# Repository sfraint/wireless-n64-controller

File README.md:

# wireless-n64-controller

## SMD Version

**This branch is for the SMD version of the controller. This is even more experimental than the original.**

**Much of the documentation is out-dated for this version, but publishing this branch for others to look at until I can polish it a bit.**

## Overview

This project and its documentation is a Work-In-Progress. I'm still working on writing everything down and working out kinks in the design files and prototypes.

**The idea is to publish the design files and software used to upgrade an OEM or cheap, wired N64 controller to a wireless, Bluetooth controller**. Hopefully these published files can assist others in completing similar projects.

## Motivation
When this project was started, no original-form-factor bluetooth N64 wireless controllers were available for purchase. There were some two-handle controllers, inspired by N64 original controllers, but none with the original three-handle setup.

The main goal of this project was to upgrade an existing OEM or cheap three-handle N64 wired controller to use bluetooth, so it could be used with a PC and/or Raspberry Pi.

## Operation

Using the controller is pretty straightforward:

1. Insert a charged battery pak into the controller to turn it on. Note: if the LED is installed, it should light up once the controller is powered on.

2. After a few seconds, pair the controller to a client machine (e.g. phone or PC). The controller should show up as `ESP32 BLE Gamepad` in bluetooth device managers. Note: if the LED is installed, it will start blinking when the controller automatically enters pairing mode after power-up.

3. If the LED is installed, it will blink slowly when the controller is paired with a client machine.

### Analog Calibration

If you press and hold the `Start` button before the controller enters pairing mode, it will enter analog calibration mode, indicated by a rapidly blinking LED.

Upon entering calibration mode, the initial position of the joystick is recorded as the new `center` position. During calibration mode, you should rotate the joystick around in circles, reaching the all the extremes (far up, right, down, left) to reset `min` and `max` values for both the X and Y axes.

Calibration mode lasts for a few seconds (~5 sec). Upon completion, it writes results to non-volatile storage if possible, then resumes normal startup routing - entering pairing mode.

### "Soft" Buttons

This wireless N64 controller has all the normal N64 buttons plus a few extra software buttons, triggered by special button combinations. These software buttons can be associated with special functions in some emulators, like triggering the menu function, save/load state, etc.

There are currently three "soft" buttons, all triggered by pressing the center of the d-pad (i.e. pressing all 4 directions at the same time) plus either `Start`, `A`, or `B`.

## Building your own
More detailed building instructions can be found [here](building.md).

*Note: this project requires soldering and some basic understanding of electriconics and circuits. I also assume you already have soldering equipment and some ~30 gauge wire to wire up components.*

### Steps

1. Purchase the base parts. See the [BOM for more details and links](BOM.md).
   * Base N64 controller you plan to modify. I'm not sure how standardized N64 controller internals are, so it is probably a good idea to confirm the measurements of your controller match up with the spacing of the PCB mounting/securing holes.
   * ESP32 microcontroller
   * AAA terminals
   * LiPo battery
   * LiPo battery charging board

2. Print the PCB.

3. Print the battery pak pieces. Alternatively, you could skip using a battery pak and directly wire a battery to the power-in on the microcontroller.

4. Program the microcontroller.

5. Solder the microcontroller and aux boards/wires to the PCB.

6. Assemble the N64 controller.

7. Have fun! (optional)

## Debugging
**Note: make sure you disconnect the battery before plugging a USB cable into the microcontroller. If you do not do this, you could permanently damage the controller or worse, whatever is on the other end of the USB cable, e.g. your PC.**

At any point, you can remove the PCB + microcontroller from the N64 controller and monitor or reprogram the microcontroller. **TODO** add debugging details.

## Components

### Microcontroller
An [ESP32](https://en.wikipedia.org/wiki/ESP32) microcontroller is used to:

1. read the raw button presses from the button hardware in the controller

2. convert that into a USB HID report

3. send the report via Bluetooth LE to a connected client, e.g. PC

It is also capable of a few other things like: tracking battery level, resetting Bluetooth connections, etc.

### PCB
A custom PCB was built to replace the existing controller PCB, mainly to a) make space for the ESP32 dev board I used and b) reduce the amount of soldering required.

### Battery Pak
A 3d-printed battery pack that fits into the controller "pak" port was used to supply power to the controller, since it can no longer pull power from the controller cable.

This "pak" fits a small lithium polymer battery as well as charging circuitry, and connects to the controller via typical AAA spring-terminals. The "pak" was designed to fit a 6mm x 40mm x 50mm battery, but could of course fit smaller batteries with adequate padding or adhesives.

## Performance

Rough performance numbers for the initial prototype controller are:

1. battery lifetime - using a ~1500 mAh lithium polymer battery, I expect the controller to last about ~15 hours of continuous use; I'm less sure about low-power mode lifetime, but probably a few weeks (longer if you just detach the battery).

2. controller latency - over 100 sequential button presses had a latency of between 2 and 13 ms (plus an additional ~2 ms for current software's polling interval - can reduce this using interrupts instead of polling, though chances are analog/jostick inputs will always suffer this extra latency)

   To measure approximate latency, I setup a second ESP32 which was:
   
   * a BLE client subscribed to the gamepad reports

   * running a GPIO interrupt to detect the button press

   Then, the second ESP32 recorded the time the button-interrupt was received as well as the time the BLE button-press-report was received. Got the approximate latency by subtracting the interrupt time from the BLE report time.

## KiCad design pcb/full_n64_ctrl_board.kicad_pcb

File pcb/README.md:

### PCB

This was designed with KiCad version 5.1.10

See [ordering](ordering.md) for details on ordering a PCB.

#### Front

#### Back

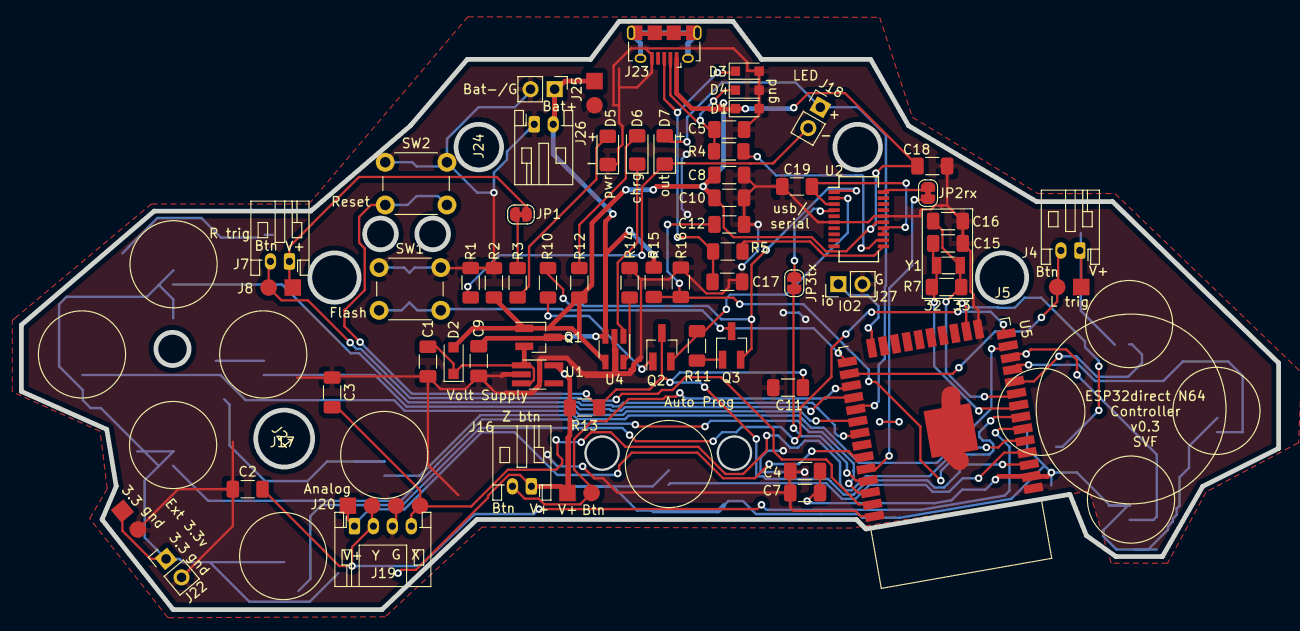
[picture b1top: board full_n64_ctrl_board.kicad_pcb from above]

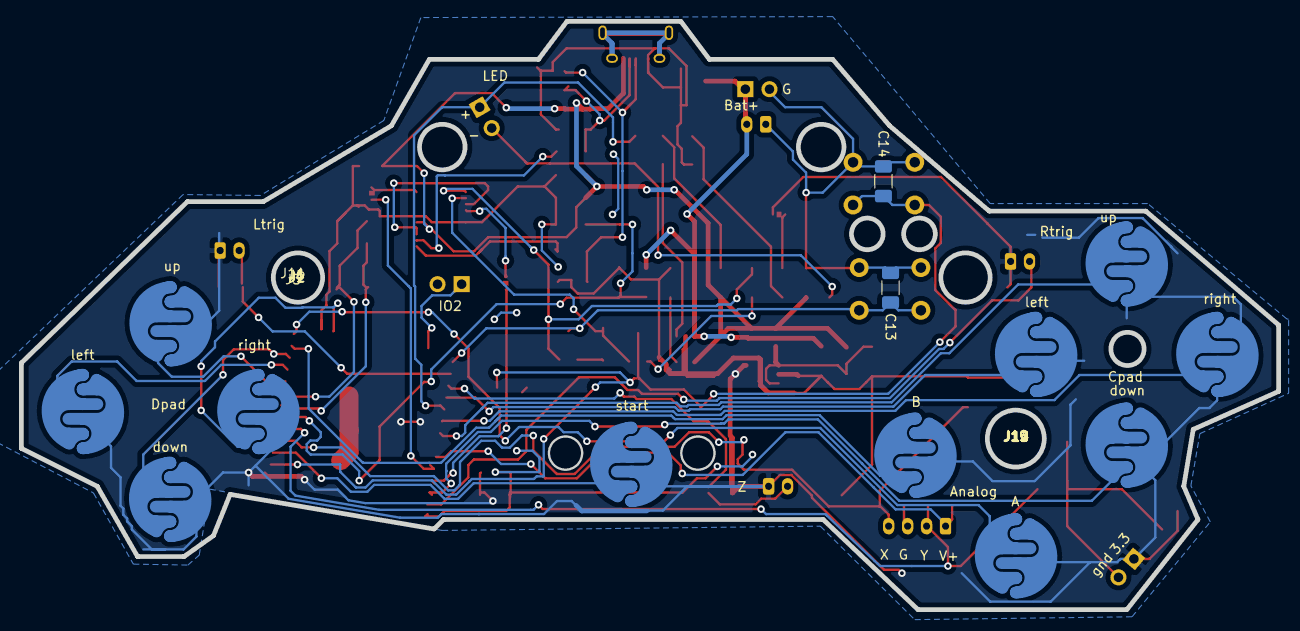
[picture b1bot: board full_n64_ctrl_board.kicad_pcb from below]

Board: 2 copper layers, 132.5 x 62.0 mm, 78 parts (13 on the bottom side), 48 nets.

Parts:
C1, C9, C10, C11, C18: 4.7uF; C_1206_3216Metric_Pad1.33x1.80mm_HandSolder
C2, C3: 0.1uF/50V; C_1206_3216Metric_Pad1.33x1.80mm_HandSolder
C4: 22uF; C_1206_3216Metric_Pad1.33x1.80mm_HandSolder
C5, C17: 47pF; C_1206_3216Metric_Pad1.33x1.80mm_HandSolder
C7, C8, C12, C13, C14, C19: 0.1uF; C_1206_3216Metric_Pad1.33x1.80mm_HandSolder
C15, C16: 7pF; C_1206_3216Metric_Pad1.33x1.80mm_HandSolder
D1, D3, D4: D_TVS; D_SOD-323_HandSoldering
D2: D_Schottky; D_SOD-123F
D5: PowerLED; LED_1206_3216Metric_Pad1.42x1.75mm_HandSolder
D6: ChargeLED; LED_1206_3216Metric_Pad1.42x1.75mm_HandSolder
D7: LEDOut; LED_1206_3216Metric_Pad1.42x1.75mm_HandSolder
J1: DpadLeftPad; n64_button_pad
J2: DpadUpPad; n64_button_pad
J3: DpadDownPad; n64_button_pad
J4: LtriggerHole; JST_PH_S2B-PH-K_1x02_P2.00mm_Horizontal
J5: LtriggerPad; 2_pad
J6: DpadRightPad; n64_button_pad
J7: RtriggerHole; JST_PH_S2B-PH-K_1x02_P2.00mm_Horizontal
J8: RtriggerPad; 2_pad
J9: BPad; n64_button_pad
J10: APad; n64_button_pad
J11: StartPad; n64_button_pad
J12: CleftPad; n64_button_pad
J13: CupPad; n64_button_pad
J14: CdownPad; n64_button_pad
J15: CrightPad; n64_button_pad
J16: ZHole; JST_PH_S2B-PH-K_1x02_P2.00mm_Horizontal
J17: ZPad; 2_pad
J18: SignalLED; PinHeader_1x02_P2.54mm_Vertical
J19: AnalogHole; JST_PH_S4B-PH-K_1x04_P2.00mm_Horizontal
J20: AnalogPad; 4_pad
J21: ExtPowerPad; 2_pad
J22: ExtPowerHole; PinHeader_1x02_P2.54mm_Vertical
J23: USB_B_Micro; USB_Micro-B_Amphenol_10118194_Horizontal
J24: ExtBatPad; 2_pad
J25: ExtBatHole; PinHeader_1x02_P2.54mm_Vertical
J26: Battery_Jumper; JST_PH_S2B-PH-K_1x02_P2.00mm_Horizontal
J27: ExtIO21; PinHeader_1x02_P2.54mm_Vertical
JP1: PowerLEDJumper; SolderJumper-2_P1.3mm_Bridged_RoundedPad1.0x1.5mm
JP2rx: RXJumper; SolderJumper-2_P1.3mm_Bridged_RoundedPad1.0x1.5mm
JP3tx: TXJumper; SolderJumper-2_P1.3mm_Bridged_RoundedPad1.0x1.5mm
Q1: Q_PMOS_GSD; SOT-23_Handsoldering
Q2, Q3: Q_NPN_BEC; SOT-23_Handsoldering
R1, R2, R3, R10, R11, R12, R13: 10k; R_1206_3216Metric_Pad1.30x1.75mm_HandSolder
R4, R5: 27; R_1206_3216Metric_Pad1.30x1.75mm_HandSolder
R7: 6.8M; R_1206_3216Metric_Pad1.30x1.75mm_HandSolder
R14: 3.3k; R_1206_3216Metric_Pad1.30x1.75mm_HandSolder
R15: 3M; R_1206_3216Metric_Pad1.30x1.75mm_HandSolder
R16: 4.7M; R_1206_3216Metric_Pad1.30x1.75mm_HandSolder
SW1, SW2: SW_Push; SW_PUSH_6mm
U1: RT9080-33GJ5; TSOT-23-5_HandSoldering
U2: FT231XS; SSOP-20_3.9x8.7mm_P0.635mm
U4: MCP73831-2-OT; SOT-23-5_HandSoldering
U5: ESP32-WROOM-32
Y1: Crystal 32.768kHz; Crystal_SMD_3215-2Pin_3.2x1.5mm

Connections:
DTR: Q3.2, R10.2, U2.1
EN: C11.1, C14.1, Q2.3, R13.2, SW2.2, U5.3
GND: C1.2, C2.1, C3.1, C4.2, C5.2, C7.2, C8.1, C9.2, C10.2, C11.2, C12.1, C13.2, C14.2, C15.2, C16.2, C17.2, C18.2, C19.2, D1.2, D3.2, D4.2, D5.1, J19.3, J20.3, J21.2, J22.2, J23.5, J24.2, J25.2, J26.1, J27.2, R1.2, R2.2, R14.1, R16.2, SW1.1, SW2.1, U1.2, U2.6, U2.16, U4.2, U5.1, U5.15, U5.38, U5.39
IO0: C13.1, Q3.3, SW1.2, U5.25
IO2: J27.1, U5.24
IO4: J4.2, J5.2, U5.26
IO5: D7.2, J18.1, U5.29
IO12: J10.2, U5.14
IO13: J6.2, U5.16
IO14: J9.2, U5.13
IO16: J16.2, J17.2, U5.27
IO17: J12.2, U5.28
IO18: J15.2, U5.30
IO19: J13.2, U5.31
IO21: J19.1, J20.1, U5.33
IO22: J14.2, U5.36
IO23: J7.2, J8.2, U5.37
IO25: J2.2, U5.10
IO26: J1.2, U5.11
IO27: J3.2, U5.12
IO32: C15.1, R7.2, U5.8, Y1.1
IO33: C16.1, R7.1, U5.9, Y1.2
IO34: C2.2, J19.2, J20.2, U5.6
IO35: C12.2, R15.1, R16.1, U5.7
unnamed: C1.1, D2.1, Q1.2, U1.1, U1.3
unnamed: C19.1, U2.3, U2.13, U2.14
unnamed: D5.2, R3.1
unnamed: D6.1, U4.1
unnamed: D6.2, R12.1
unnamed: D7.1, J18.2, R1.1
unnamed: JP1.1, R3.2
unnamed: JP2rx.1, U2.20
unnamed: JP3tx.1, U2.4
unnamed: Q2.1, R10.1
unnamed: Q3.1, R11.1
unnamed: R4.1, U2.12
unnamed: R5.1, U2.11
unnamed: R14.2, U4.5
RTS: Q2.2, R11.2, U2.2
RXD0: JP2rx.2, U5.34
SENSOR_VN: C3.2, J19.4, J20.4, U5.5
SENSOR_VP: J11.2, U5.4
TXD0: JP3tx.2, U5.35
USB_DN: C5.1, D4.1, J23.2, R4.2
USB_DP: C17.1, D3.1, J23.3, R5.2
VBAT: C9.1, J24.1, J25.1, J26.2, Q1.3, R15.2, U4.3
VBUS: C8.2, C10.1, C18.1, D1.1, D2.2, J23.1, Q1.1, R2.1, R12.2, U2.15, U4.4
VDD: C4.1, C7.1, J1.1, J2.1, J3.1, J4.1, J5.1, J6.1, J7.1, J8.1, J9.1, J10.1, J11.1, J12.1, J13.1, J14.1, J15.1, J16.1, J17.1, J21.1, J22.1, JP1.2, R13.1, U1.5, U5.2

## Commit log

2021-11-07 initial skeleton
2021-11-08 reorg
2021-11-08 add initial gamepad software
2021-11-08 software instructions
2021-11-08 Create LICENSE
2021-11-08 pic update
2021-11-08 Update README.md
    latency note
2021-11-09 Update README.md
    latency methodology
2021-11-13 larger stack for input poll loop, more analog sensitivity, debug printing
2021-11-15 add info about software versions
2021-11-20 cleanup/clarify button mapping
2021-11-22 add soft buttons
2021-11-23 add battery level logic, reset debug flag
2021-11-24 update files
2021-11-24 update readmes and docs
2021-11-24 Clarification
2021-11-24 Fix links
2021-11-25 update installed PCB image
2021-11-26 fix pin mapping and conflicts
2021-12-02 update PCB, update button mapping, re-enable battery level setup
2021-12-05 BOM and readme simplifications
2021-12-05 update images
2021-12-05 relative links
2021-12-05 more detailed build instructions
2021-12-05 details
2021-12-06 update wording
2021-12-06 wording
2021-12-07 simplify instructions
2021-12-07 more clarification
2021-12-07 Lite-board detailed building instructions (#5)
    * BOM and readme simplifications
    * update images
    * more detailed build instructions
2021-12-07 Fix typos
2021-12-26 switch to more debug statements
2021-12-27 poll helpers
2021-12-27 update LED indicator behavior; solid startup, flash waiting for BT, slow flash when connected
2022-01-02 formatting
2022-01-03 calibration with persistent storage, use calibration values in analog polling
2022-01-03 Optional -> Recommended parts
    Make optional parts recommended instead. Note: I've now had some issues with the `start` button after extended use on one of the prototype controllers (registering erroneous button presses occasional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
2022-01-03 More explicit project settings
    Add more explicit project settings for `idf.py menuconfig`
2022-01-16 Add Operation details
    Add details about Operation, Analog calibration, "Soft" buttons
2022-02-15 add latency test code
2022-09-03 add software build workflow
2022-09-03 add test step
2022-09-03 triggers
2022-09-03 fix path, suppress output a bit, add linux version
2022-09-03 try win
2022-09-03 indent
2022-09-03 try w va
2022-09-03 with cwd
2022-09-03 invoke path
2022-09-03 comment out win build, add action-based build
2022-09-03 skip checkout
2022-09-03 more triggers
2022-09-03 remove test branch, rename main build step
2022-09-03 CI: add workflow to build ESP32 software project (#6)
    add software build workflow
2022-09-03 fix software readme typo
2022-09-03 make config optional, reference specific version of NimBLE, more detailed instructions
2022-09-03 Update README.md
    optional note, punctuation
2022-09-03 SW Readme: More specific setup instructions (#7)
    make config optional, reference specific version of NimBLE, more detailed instructions
2023-02-28 Added first cut of SIXPIN Joysitck
2023-02-28 Improved Commenting
2023-03-05 Updated to utilise scaling and calibration
2023-03-05 Add docker build instructions
2023-03-06 Refactored and added Calibration for SIXPIN
2023-03-11 Skip Mac tests
    Mac tests are failing, just skip them until they're debugged
2023-03-31 Update to resolve PR comments
2023-03-31 Disabled SIXPIN
2023-04-01 updated comments and defaults
2023-04-01 Updated main README
2023-04-01 Updated build readme
2023-04-01 Upload image joystick PCB
2023-04-01 Update Images for 6pin
2023-04-02 Disabled Bat functionality if SIXPIN is enabled
2023-04-02 Updated to use abs() vs custom function
2023-04-26 Updated to remove factor* and sixpin calibration
2023-05-01 Updated based on PR Feedback
2023-05-27 Update input_poll.h
    set 4 pin default
2023-05-28 6pin n64 Joystick option (#9)
    Add support for SIXPIN, digital Joysitck
2023-11-23 add sleep, update for SMD rev
2023-11-23 log level, auto sleep, C-soft-button
2023-11-23 cleanup unused code, fix warnings
2024-12-19 Update with experimental PCB
